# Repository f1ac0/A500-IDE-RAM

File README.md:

# A500-IDE-RAM
This is an expansion for Amiga 500 and plus providing 2MB Fast SRAM and one IDE port. I believe the two things that the A500 lacks the most are probably a hard drive, and Fast RAM.

The RAM is configured by default as 2MB Fast autoconfig (in the 200000-9FFFFF space), and it can be turned into a 1.5MB (fast) RAM in ranger space (C00000-D7FFFF) together with 512KB MapROM. This mode is targeted for owners of plus or expanded rev8a who want to play old picky games from floppies. The modes and maprom can be configured by maintaining the reset from 3 to 10s or by using the provided Amiga software.

Facts about this project :
- It sits under the CPU : does not block access to the ROM and does not need a relocator.
- I wanted a mini-IDE port, this is the main reason why I started to create my own board.
- I thought that it would be neat to have some Fast RAM on the same 2-layers PCB, and I had a great SRAM chip for another project, PCMCIA-SRAM.
- The IDE port simulates the one from the A600 so it is bootable with appropriate Kickstarts. Like other IDE expansions, it requires two additional signals from the motherboard : INT2 and OVR.
- By default, the RAM stuff takes the place of the first expansion in the autoconfig chain. To use other autoconfig expansions, you need to configure the firmware with config_in/out pins to put it in your autoconfig chain ; these pins take the place of the secondary LED.
- Version 0.3 of the board adds a "clockport" to connect compatible expansions. Its "SPARE_CS" is at address D8xxxx. It is untested at the time of writing

# Acknowledgements
Thanks Guys :
- mkl from http://www.mkl211015.altervista.org has created both IDE and RAM expansions, ide68k and ram68k, that sit under the 68000, and can be stacked. I thank him for publishing his schematic and code since it inspired this project, and the base of the IDE CPLD code is a verilog conversion I made from his abel of version 425.
- Sector101 shared an interesting experiment that proved it is somewhat simple to use SRAM as fast memory, and encouraged me to try adding it to this project : https://blog.sector101.co.uk/2019/07/20/amiga-500-2mb-handwired-fastram-expansion/ .
- Sukkopera shared the OpenAmiga500FastRamExpansion from which I used the autoconfig CPLD code in earlier versions : https://github.com/SukkoPera/OpenAmiga500FastRamExpansion/
- the software in this project is inspired by the MapROM tool shared by Paul RASPA (PR77) https://github.com/PR77/A600_ACCEL_RAM/tree/master/Software . This is the first C code I ever compiled for my Amiga, so I believe the MapROM function was achieved thanks to this working starting point !

# Disclaimer
This is a hobbyist project, it comes with no warranty and no support. Also remember that the Amiga machines are about 30 years old and may fail because of such hardware expansions.

I publish my work under the CC-BY-NC-SA license. The content of this repository is the result of weeks of work, requiring investment in tools, parts, prototypes, and risky tests on his own equipment. For this reason the author does not want third parties to sell products and keep all the profit, usually without even offering support to their customers. If you see people selling this without the consent of the author, don't buy from them.

If you find it useful and want to reward my hard work : I am always looking for Amiga/Amstrad CPC hardware to repair and hack, please contact me.

# BOM
- 1x XC95144XL CPLD
- 1x CY62167ELL-45ZXI 5V SRAM (do not use 3.3V CY62167EV !). For 4MB you may also, with small changes in the CPLD code (addressing and autoconfig) :
 - stack a second chip on the first one and connect its pin 12 to the pad nearby -god skills required-,
 - use a CY62177ESL-55ZXI 5V SRAM instead (rare, expensive, not tested).
- 1x 3.3v LDO, either SPX3819M5-L-3-3 or XC6206P332MR
- 2x 1uF (or more) 0805 capacitors
- 5x 100nF 0805 capacitors
- 3x 10k 0805 resistors
- 2x 4k7 0805 resistors
- 1x BAT54A (or equivalent) diodes
- 64x rounded socket pins, for CPU pass-through connection. I use pins taken from a socket header.
- 1x 2x22 2.0mm pin header. Remove pin 20 which is IDE key.
- 2x wires for INT2 and OVR signals
- optional : 1x LED and resistor (330 ohm 0805 for example)

# Making it
Components are SMD, and have thin pin pitch. You need to know what you are doing.

Check for shorts at least between 5V, 3.3V, and GND traces before applying power !

The programming port does not need to be soldered since it needs to be programmed just once : you can just hold it in place during the few seconds required for programming.

CPLD code is generated and built into xsvf using Xilinx ISE 14.7 IDE then iMPACT. There are configuration defines for RAM type and LED/config_pins selection, choose the ones you need. The "Process Properties" of the Fitting step are tweaked :
- -slew = Slow
- -power = Low
- -nogclkopt = Checked (by default)
- -nogsropt = Checked (by default)
- -unused = NOT Checked (by default), since pin 4 is used as pass-through

There are several methods to program the XC95144XL, I personally use xsvfduino. I advise you program it when unplugged from the motherboard, otherwise make sure to power it from the motherboard and not your programmer or it might burn trying to power the whole system.

# Using it
- Remove the 68000 CPU from the motherboard
- Insert the CPU on the expansion. I personally upgraded to a 68010 to gain the quit key ability with WHDLoad
- Plug the expansion in the motherboard. Take care of Pin 1. Push it firmly so it does not pop out of the socket during use, but do not break the CPU socket.
- Connect INT2 and OVR headers to the motherboard
- On the v0.3 board, connect INT6 to use the clockport expansions that need it
- Turn on the Amiga

Maintaining the reset for a few seconds will allow you to :
- 3s : disable MapROM for the next reboot
- 6s : turn off MapROM
- 10s : toggle the ram mode

# Amiga FLACOntrol Software
You may use the provided FLACOntrol software to control the board from your OS. It exists in several flavours, with classic or unix-like command line arguments, or silent with minimal text output.

It provides a MapROM function that writes a 256K or 512K ROM image to F80000-FFFFFF.
It also communicates with this expansion using a control register byte at $00E9Cxxx :
- bit 7 indicates if MapROM is active, write 0 to disable it at next reboot ;
- bit 6 is the current ram mode, 0 for Fast autoconfig and 1 for Ranger MapROM ; write it to change mode at next reboot.

To activate Ranger RAM with MapROM ; this will take effect at next reboot :
```
FLACOntrol -1
```
To map the internal ROM (might speed up the system) :
```
FLACOntrol -i
```
Or a different ROM from file, 256K and 512K are supported :
```
FLACOntrol -f Files:path/kickstart-image-not-swapped-nor-split.rom
```
It will revert to the hardware ROM at next power cycle or with :
```
FLACOntrol -x
```
And revert to the full autoconfig RAM and reboot immediately to take effect :
```
FLACOntrol -0 -r
```

To use the MapROM function more extensively, you may compile the CPLD firmware to provide MapROM by default, then add the following line to your startup-sequence. The -r flag tells the software to reboot the system after the new ROM is loaded, then during next reboot the software will exit since MapROM is already active, and your system will finish to boot with the new ROM :
```
FLACOntrol -f Files:path/kickstart-image-not-swapped-nor-split.rom -r
```

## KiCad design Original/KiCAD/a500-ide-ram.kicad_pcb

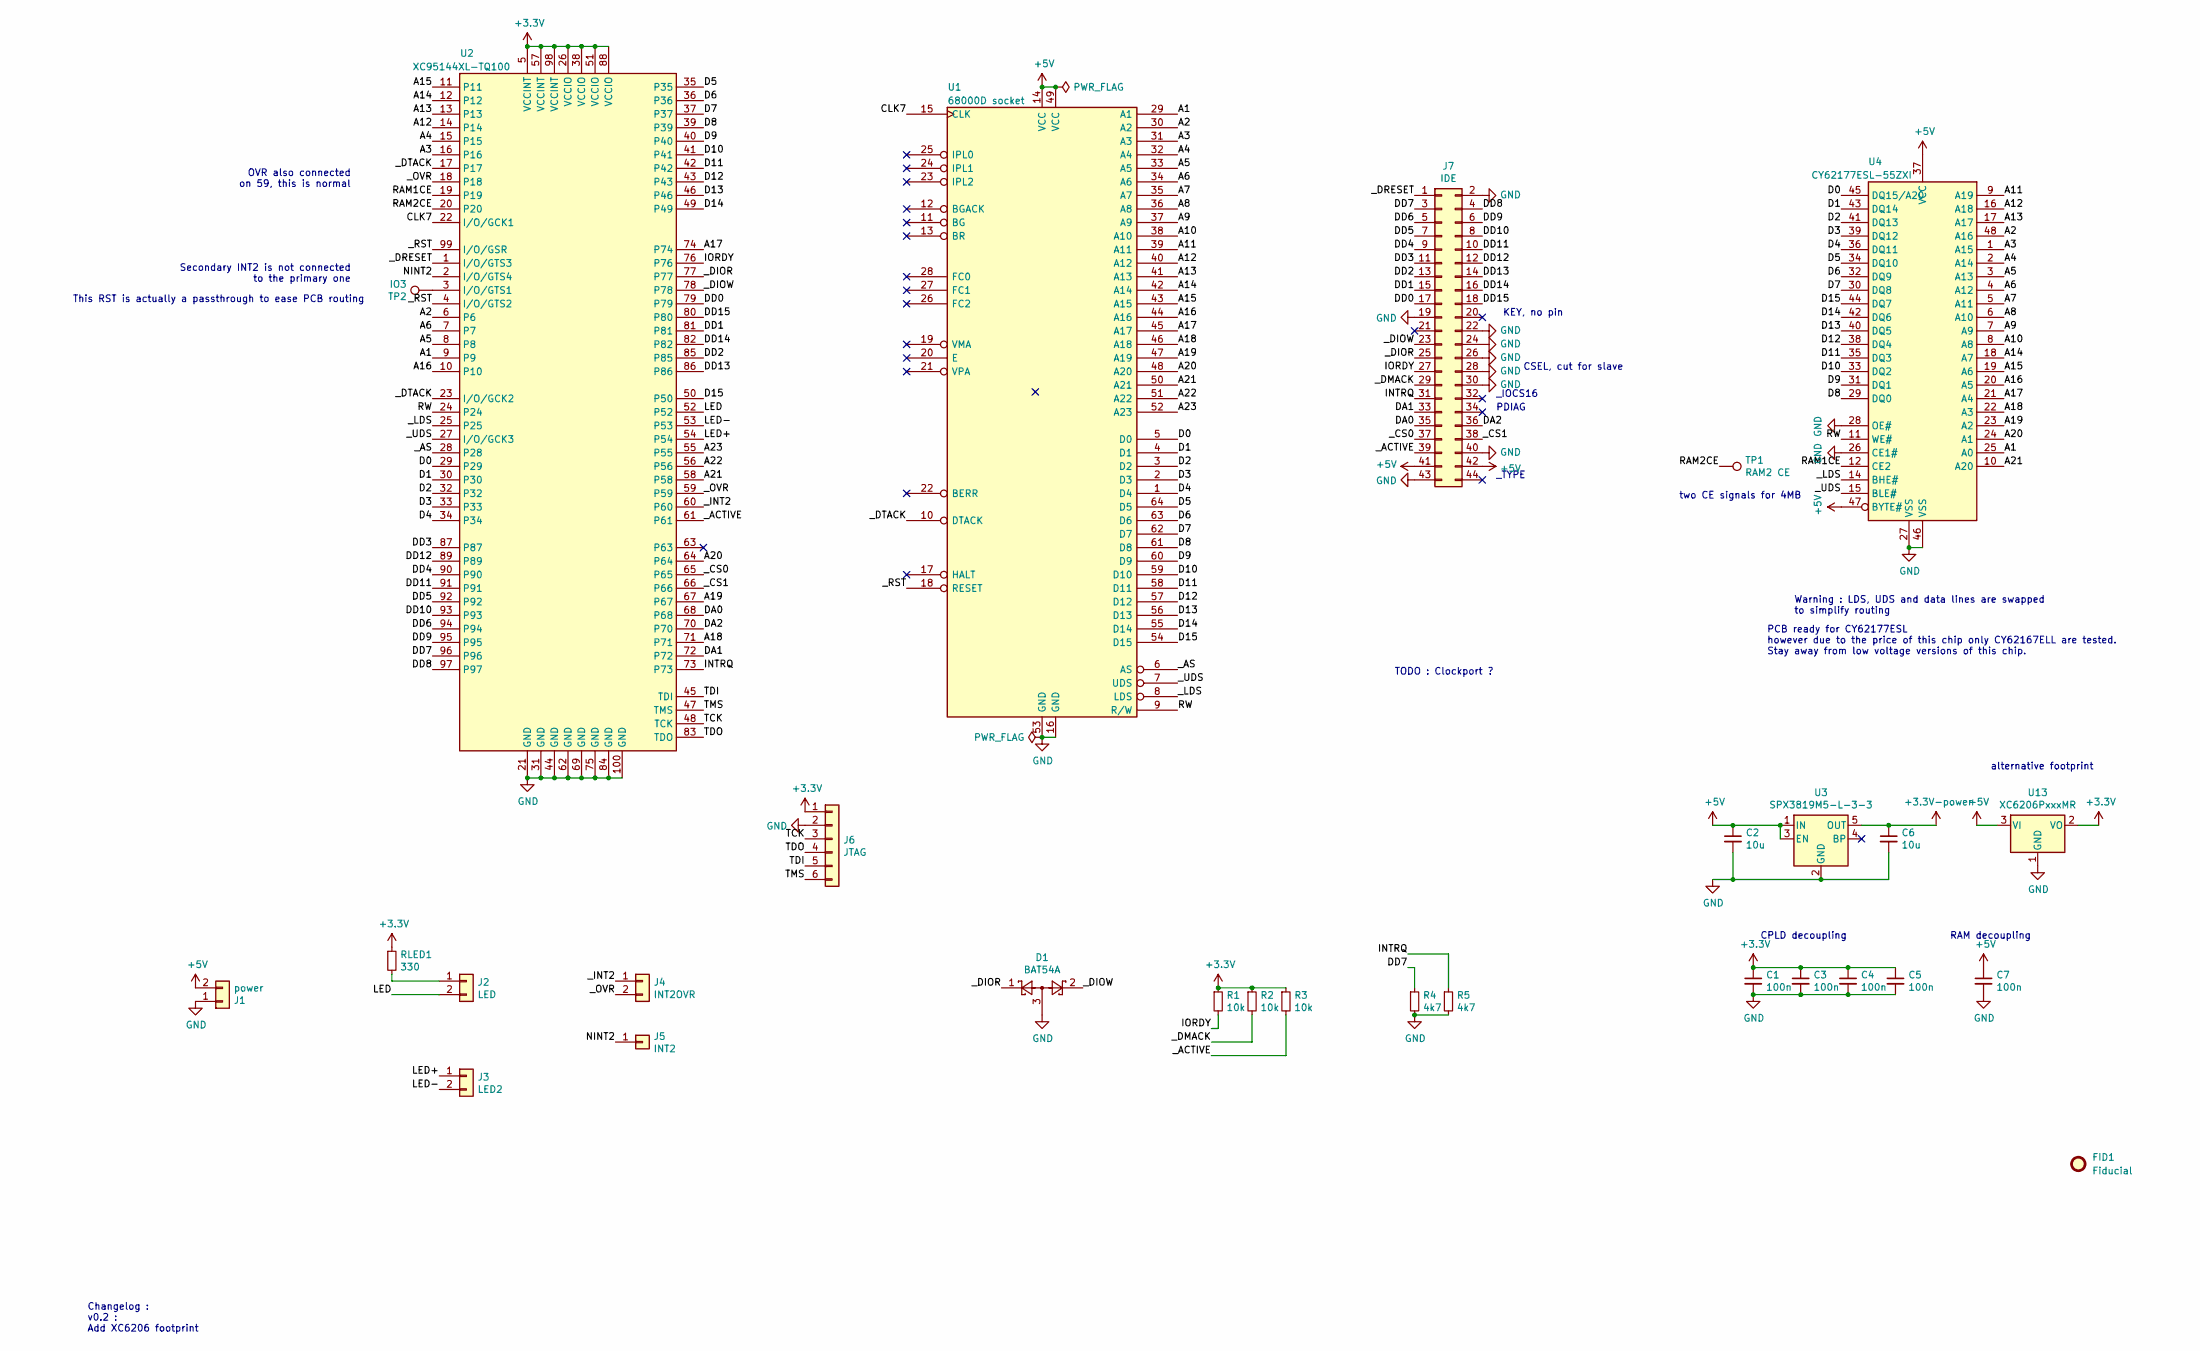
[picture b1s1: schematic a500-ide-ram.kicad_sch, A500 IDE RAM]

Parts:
C1, C3, C4, C5, C7: 100n; C_0805_2012Metric
C2, C6: 10u; C_0805_2012Metric
D1: BAT54A; SOT-23
FID1: Fiducial; CC_BY_NC_SA_square_silkscreen
J1: power; PinHeader_1x02_P2.54mm_Vertical
J2: LED; PinHeader_1x02_P2.54mm_Vertical
J3: LED2; PinHeader_1x02_P2.54mm_Vertical
J4: INT2OVR; PinHeader_1x02_P2.54mm_Vertical
J5: INT2; PinHeader_1x01_P2.54mm_Vertical
J6: JTAG; PinHeader_1x06_P2.54mm_Vertical
J7: IDE; PinHeader_2x22_P2.00mm_Vertical
R1, R2, R3: 10k; R_0805_2012Metric
R4, R5: 4k7; R_0805_2012Metric
RLED1: 330; R_0805_2012Metric
TP1: RAM2 CE; TestPoint_Pad_D1.0mm
TP2: IO3; PinHeader_1x01_P2.54mm_Vertical
U1: 68000D socket; DIP-64_W22.86mm_BigPads1.4
U2: XC95144XL-TQ100; TQFP-100_14x14mm_P0.5mm
U3: SPX3819M5-L-3-3; SOT-23-5
U4: CY62177ESL-55ZXI; TSOP-I-48_18.4x12mm_P0.5mm
U13: XC6206PxxxMR; SOT-23

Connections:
+5V: C2.1, C7.1, J1.2, J7.41, J7.42, U1.14 (VCC), U1.49 (VCC), U3.1 (IN), U3.3 (EN), U4.37 (VCC), U4.47 (BYTE#), U13.3 (VI)
/A1: U1.29 (A1), U2.9, U4.25 (A0)
/A2: U1.30 (A2), U2.6, U4.48 (A16)
/A3: U1.31 (A3), U2.16, U4.1 (A15)
/A4: U1.32 (A4), U2.15, U4.2 (A14)
/A5: U1.33 (A5), U2.8, U4.3 (A13)
/A6: U1.34 (A6), U2.7, U4.4 (A12)
/A7: U1.35 (A7), U4.5 (A11)
/A8: U1.36 (A8), U4.6 (A10)
/A9: U1.37 (A9), U4.7 (A9)
/A10: U1.38 (A10), U4.8 (A8)
/A11: U1.39 (A11), U4.9 (A19)
/A12: U1.40 (A12), U2.14, U4.16 (A18)
/A13: U1.41 (A13), U2.13, U4.17 (A17)
/A14: U1.42 (A14), U2.12, U4.18 (A7)
/A15: U1.43 (A15), U2.11, U4.19 (A6)
/A16: U1.44 (A16), U2.10, U4.20 (A5)
/A17: U1.45 (A17), U2.74, U4.21 (A4)
/A18: U1.46 (A18), U2.71, U4.22 (A3)
/A19: U1.47 (A19), U2.67, U4.23 (A2)
/A20: U1.48 (A20), U2.64, U4.24 (A1)
/A21: U1.50 (A21), U2.58, U4.10 (A20)
/A22: U1.51 (A22), U2.56
/A23: U1.52 (A23), U2.55
/CLK7: U1.15 (CLK), U2.22 (I/O/GCK1)
/D0: U1.5 (D0), U2.29, U4.45 (DQ15/A20)
/D1: U1.4 (D1), U2.30, U4.43 (DQ14)
/D2: U1.3 (D2), U2.32, U4.41 (DQ13)
/D3: U1.2 (D3), U2.33, U4.39 (DQ12)
/D4: U1.1 (D4), U2.34, U4.36 (DQ11)
/D5: U1.64 (D5), U2.35, U4.34 (DQ10)
/D6: U1.63 (D6), U2.36, U4.32 (DQ9)
/D7: U1.62 (D7), U2.37, U4.30 (DQ8)
/D8: U1.61 (D8), U2.39, U4.29 (DQ0)
/D9: U1.60 (D9), U2.40, U4.31 (DQ1)
/D10: U1.59 (D10), U2.41, U4.33 (DQ2)
/D11: U1.58 (D11), U2.42, U4.35 (DQ3)
/D12: U1.57 (D12), U2.43, U4.38 (DQ4)
/D13: U1.56 (D13), U2.46, U4.40 (DQ5)
/D14: U1.55 (D14), U2.49, U4.42 (DQ6)
/D15: U1.54 (D15), U2.50, U4.44 (DQ7)
/DA0: J7.35, U2.68
/DA1: J7.33, U2.72
/DA2: J7.36, U2.70
/DD0: J7.17, U2.79
/DD1: J7.15, U2.81
/DD2: J7.13, U2.85
/DD3: J7.11, U2.87
/DD4: J7.9, U2.90
/DD5: J7.7, U2.92
/DD6: J7.5, U2.94
/DD7: J7.3, R4.1, U2.96
/DD8: J7.4, U2.97
/DD9: J7.6, U2.95
/DD10: J7.8, U2.93
/DD11: J7.10, U2.91
/DD12: J7.12, U2.89
/DD13: J7.14, U2.86
/DD14: J7.16, U2.82
/DD15: J7.18, U2.80
/INTRQ: J7.31, R5.1, U2.73
/IORDY: J7.27, R1.2, U2.76
/LED: J2.2, U2.52
/LED+: J3.1, U2.54
/LED-: J3.2, U2.53
/NINT2: J5.1, U2.2 (I/O/GTS4)
/RAM1CE: U2.19, U4.12 (CE2)
/RAM2CE: TP1.1, U2.20
/RW: U1.9 (R/W), U2.24, U4.11 (WE#)
/TCK: J6.3, U2.48 (TCK)
/TDI: J6.5, U2.45 (TDI)
/TDO: J6.4, U2.83 (TDO)
/TMS: J6.6, U2.47 (TMS)
/_ACTIVE: J7.39, R3.2, U2.61
/_AS: U1.6 (AS), U2.28
/_CS0: J7.37, U2.65
/_CS1: J7.38, U2.66
/_DIOR: D1.1, J7.25, U2.77
/_DIOW: D1.2, J7.23, U2.78
/_DMACK: J7.29, R2.2
/_DRESET: J7.1, U2.1 (I/O/GTS3)
/_DTACK: U1.10 (DTACK), U2.17, U2.23 (I/O/GCK2)
/_INT2: J4.1, U2.60
/_LDS: U1.8 (LDS), U2.25, U4.14 (BHE#)
/_OVR: J4.2, U2.18, U2.59
/_RST: U1.18 (RESET), U2.4 (I/O/GTS2), U2.99 (I/O/GSR)
/_UDS: U1.7 (UDS), U2.27 (I/O/GCK3), U4.15 (BLE#)
GND: C1.2, C2.2, C3.2, C4.2, C5.2, C6.2, C7.2, D1.3, J1.1, J6.2, J7.2, J7.19, J7.22, J7.24, J7.26, J7.28, J7.30, J7.40, J7.43, R4.2, R5.2, U1.16 (GND), U1.53 (GND), U2.21 (GND), U2.31 (GND), U2.44 (GND), U2.62 (GND), U2.69 (GND), U2.75 (GND), U2.84 (GND), U2.100 (GND), U3.2 (GND), U4.26 (CE1#), U4.27 (VSS), U4.28 (OE#), U4.46 (VSS), U13.1 (GND)
unnamed: J2.1, RLED1.2
unnamed: TP2.1, U2.3 (I/O/GTS1)

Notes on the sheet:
PDIAG
TODO : Clockport ?
alternative footprint
CPLD decoupling
two CE signals for 4MB
CSEL, cut for slave
This RST is actually a passthrough to ease PCB routing
_TYPE
Secondary INT2 is not connected to the primary one
KEY, no pin
Warning : LDS, UDS and data lines are swapped to simplify routing
RAM decoupling
Changelog : v0.2 : Add XC6206 footprint
OVR also connected on 59, this is normal
PCB ready for CY62177ESL however due to the price of this chip only CY62167ELL are tested. Stay away from low voltage versions of this chip.
_IOCS16

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
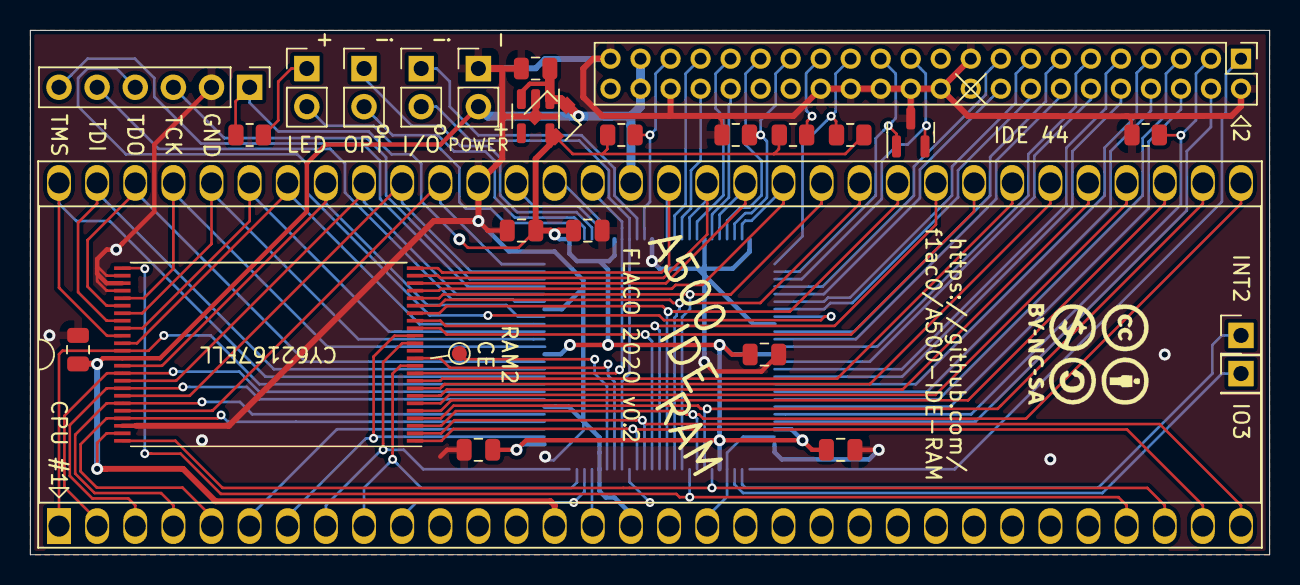
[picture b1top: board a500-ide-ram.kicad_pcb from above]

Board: 2 copper layers, 82.5 x 34.9 mm, 29 parts (1 on the bottom side), 91 nets.

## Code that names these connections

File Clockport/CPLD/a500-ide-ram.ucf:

# A500-IDE-RAM-CLOCKPORT

NET _AS LOC=P28;
NET R_W LOC=P24;
NET _UDS LOC=P27;
NET _LDS LOC=P25;
NET _DTACK LOC=P23;
NET _DTACK2 LOC=P17;
NET _OVR PWR_MODE=STD;
NET _OVR FAST;
NET _OVR LOC=P59;
NET _OVR2 PWR_MODE=STD;
NET _OVR2 FAST;
NET _OVR2 LOC=P18;
NET _INT2 LOC=P60;
NET _RESET LOC=P99;
NET CLK LOC=P22;
NET AH<23> LOC=P52;
NET AH<22> LOC=P54;
NET AH<21> LOC=P58;
NET AH<20> LOC=P64;
NET AH<19> LOC=P67;
NET AH<18> LOC=P71;
NET AH<17> LOC=P74;
NET AH<16> LOC=P10;
NET AH<15> LOC=P11;
NET AH<14> LOC=P12;
NET AH<13> LOC=P13;
NET AH<12> LOC=P14;
NET AL<6> LOC=P7;
NET AL<5> LOC=P8;
NET AL<4> LOC=P15;
NET AL<3> LOC=P16;
NET AL<2> LOC=P6;
NET AL<1> LOC=P9;
NET D<15> LOC=P50;
NET D<14> LOC=P49;
NET D<13> LOC=P46;
NET D<12> LOC=P43;
NET D<11> LOC=P42;
NET D<10> LOC=P41;
NET D<9> LOC=P40;
NET D<8> LOC=P39;
NET D<7> LOC=P37;
NET D<6> LOC=P36;
NET D<5> LOC=P35;
NET D<4> LOC=P34;
NET D<3> LOC=P33;
NET D<2> LOC=P32;
NET D<1> LOC=P30;
NET D<0> LOC=P29;

//NET IORDY LOC=P73;
NET INTRQ LOC=P72;
NET _ACTIVE LOC=P61;
NET DD[7] LOC=P95;
NET DD[6] LOC=P93;
NET DD[5] LOC=P91;
NET DD[4] LOC=P89;
NET DD[3] LOC=P86;
NET DD[2] LOC=P82;
NET DD[1] LOC=P80;
NET DD[0] LOC=P78;
NET DD[15] LOC=P79;
NET DD[14] LOC=P81;
NET DD[13] LOC=P85;
NET DD[12] LOC=P87;
NET DD[11] LOC=P90;
NET DD[10] LOC=P92;
NET DD[9] LOC=P94;
NET DD[8] LOC=P96;
NET _DRESET LOC=P97;
NET DA<2> LOC=P68;
NET DA<1> LOC=P70;
NET DA<0> LOC=P66;
NET _CS[1] LOC=P65;
NET _CS[0] LOC=P63;
NET _DIOW LOC=P77;
NET _DIOR LOC=P76;

NET _LED LOC=P53;
NET OPTPIN_O LOC=P55;
NET OPTPIN_I LOC=P56;
NET RAM1CE LOC=P19;
NET RAM2CE LOC=P20;

NET _IORD LOC=P2;
NET _IOWR LOC=P3;
NET _SPARE_CS LOC=P1;

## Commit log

2020-08-28 Respository init with v0.1 KiCAD files, CPLD source, Readme and License
2021-02-13 Updated CPLD code with new autoconfig, new ranger-maprom, rewritten IDE ; new MapROM software ; 0.2 hardware
2021-02-15 Updated MapROM software with working ColdReboot for ks1.3 ; added bootable floppy image to unMapROM
2021-02-15 Software bug : would not reboot after a MapROM from file
2021-02-16 Combo firmware and software to provide configurable autoconfig fast RAM or ranger MapROM without reprogramming the CPLD
2021-02-18 Cosmetic indenting cleanup
2021-02-19 Added to software a config register to force 4MB mode for A1200FaStRamExpansion
2021-02-24 Rename software since it now provides features besides MapROM ; include an AddMem tool for A1200FaStRamExpansion
2021-02-25 Simplified and cleaned software code, now compile without warning ; include alternative versions with classic ReadArgs arguments and less verbose
2021-07-30 CPLD firmware : export IDE as a module ; add dtack to control_access in ram_combo
2021-08-31 CPLD firmware update : MapROM disable and Mode change using reset duration
2022-10-18 Change project name to match other projects. Kicad: conversion to Kicad 6, repo URL on PCB silkscreen.
2022-10-18 Public repository init with schematic, Gerbers, ibom, CPLD xsvf, Software, Photo, Readme, License
2022-10-22 KiCAD : correct license on schematic and PCB
2023-06-14 Addition of v0.3 with clockport KiCAD and CPLD files. v0.2 has been moved to the "Original" subdirectory.
2023-06-28 CPLD : forgot DTACK for clockport

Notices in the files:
Clockport/KiCAD/a500-ide-ram.kicad_sch:
FLACO 2020-2023 CC-BY-NC-SA
Original/KiCAD/a500-ide-ram.kicad_pcb:
FLACO 2020 CC-BY-NC-SA
